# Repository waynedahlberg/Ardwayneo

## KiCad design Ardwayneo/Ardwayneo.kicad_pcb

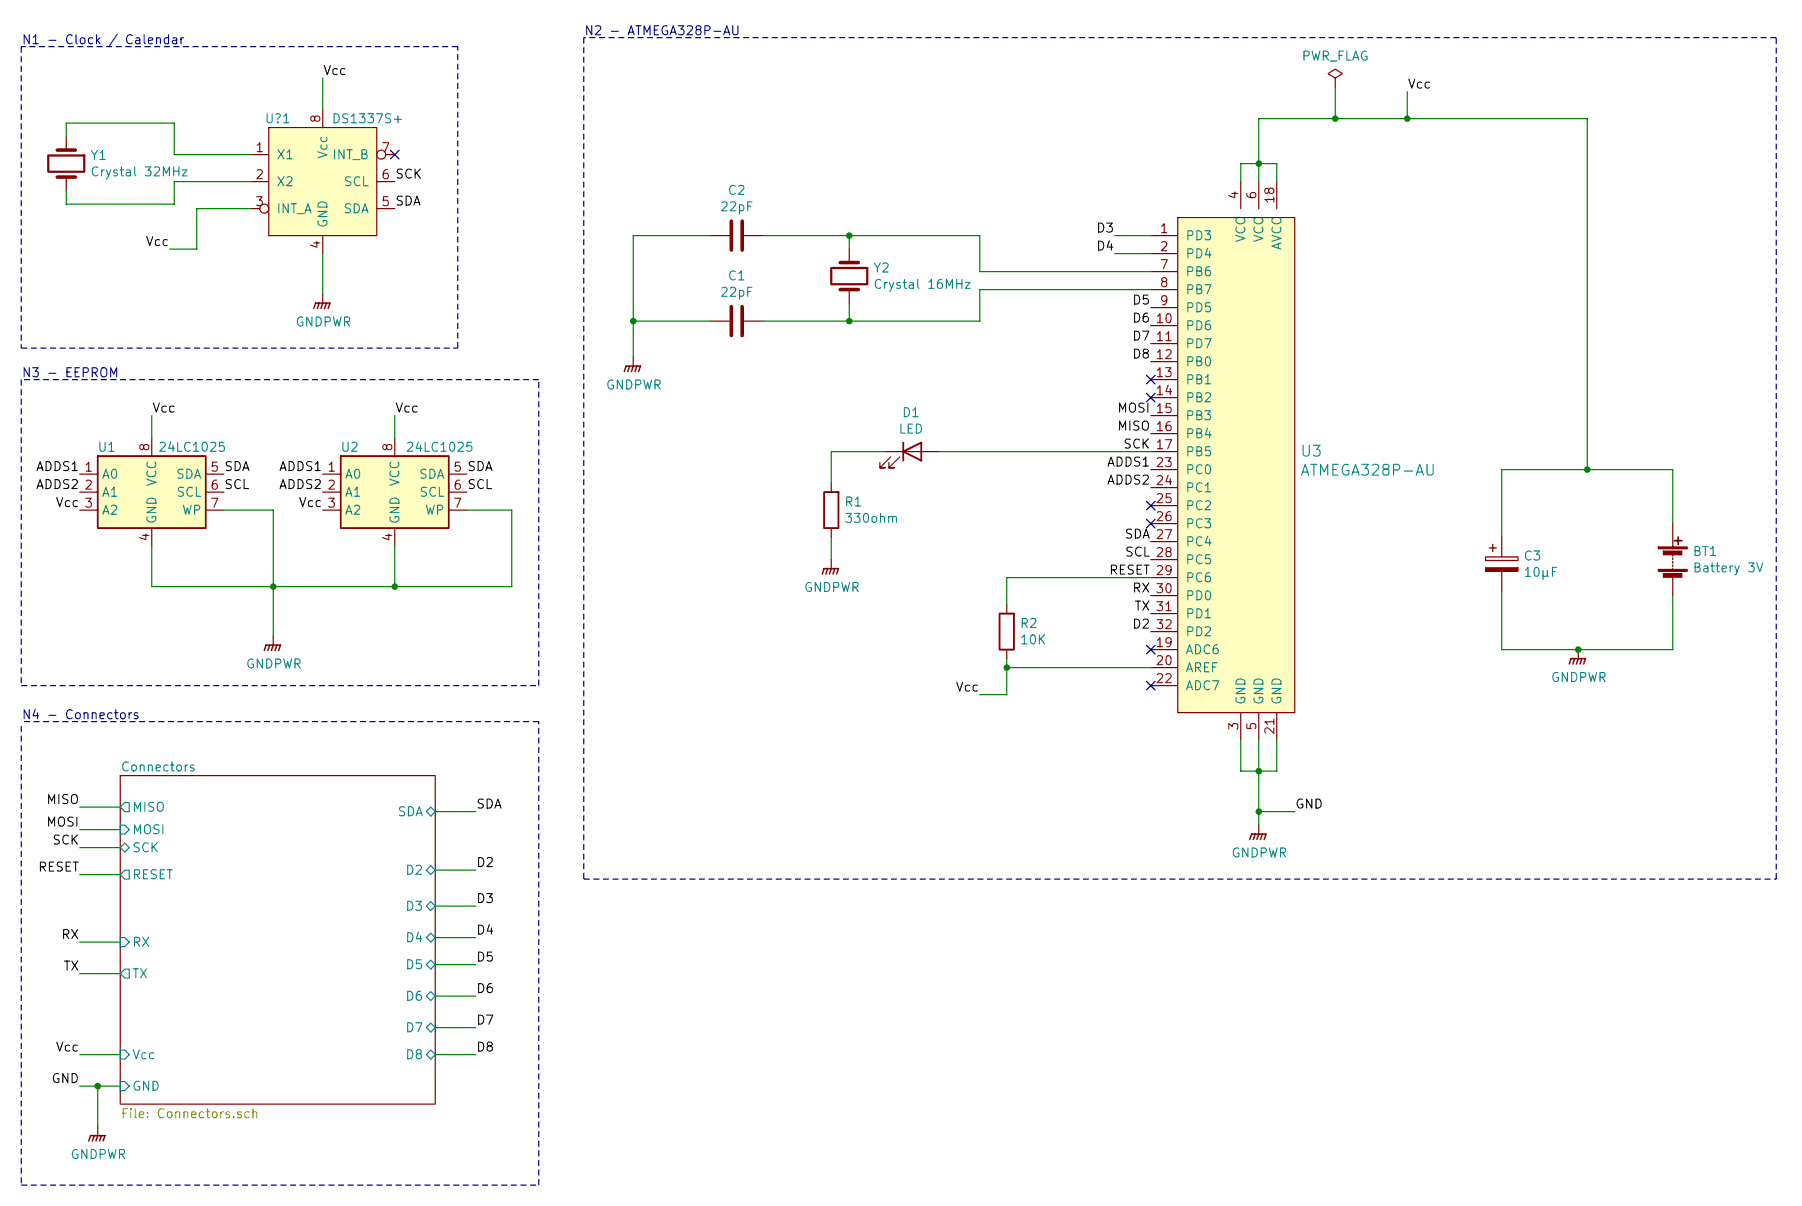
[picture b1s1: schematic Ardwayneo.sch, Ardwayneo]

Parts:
BT1: Battery 3V; PinHeader_1x02_P2.54mm_Vertical
C1, C2: 22pF; C_0805_2012Metric_Pad1.18x1.45mm_HandSolder
C3: 10µF; C_0805_2012Metric_Pad1.18x1.45mm_HandSolder
D1: LED; LED_0805_2012Metric_Pad1.15x1.40mm_HandSolder
R1: 330ohm; R_0805_2012Metric_Pad1.20x1.40mm_HandSolder
R2: 10K; R_0805_2012Metric_Pad1.20x1.40mm_HandSolder
U1, U2: 24LC1025; SOIJ-8_5.3x5.3mm_P1.27mm
U3: ATMEGA328P-AU; TQFP-32_7x7mm; MPN ATMEGA328P-AU; Digi-Key_PN ATMEGA328P-AU-ND
U?1: DS1337S+; SO-8_5.3x6.2mm_P1.27mm
Y1: Crystal 32MHz; Crystal_SMD_MicroCrystal_CC7V-T1A-2Pin_3.2x1.5mm
Y2: Crystal 16MHz; Crystal_SMD_5032-2Pin_5.0x3.2mm_HandSoldering

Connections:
/ADDS1: U1.1 (A0), U2.1 (A0), U3.23 (PC0)
/ADDS2: U1.2 (A1), U2.2 (A1), U3.24 (PC1)
/D2: U3.32 (PD2); also elsewhere on the board
/D3: U3.1 (PD3); also elsewhere on the board
/D4: U3.2 (PD4); also elsewhere on the board
/D5: U3.9 (PD5); also elsewhere on the board
/D6: U3.10 (PD6); also elsewhere on the board
/D7: U3.11 (PD7); also elsewhere on the board
/D8: U3.12 (PB0); also elsewhere on the board
/MISO: U3.16 (PB4); also elsewhere on the board
/MOSI: U3.15 (PB3); also elsewhere on the board
/RESET: R2.2, U3.29 (PC6); also elsewhere on the board
/RX: U3.30 (PD0); also elsewhere on the board
/SCK: D1.2 (A), U3.17 (PB5), U?1.6 (SCL); also elsewhere on the board
/SCL: U1.6 (SCL), U2.6 (SCL), U3.28 (PC5)
/SDA: U1.5 (SDA), U2.5 (SDA), U3.27 (PC4), U?1.5 (SDA); also elsewhere on the board
/TX: U3.31 (PD1); also elsewhere on the board
/Vcc: BT1.1 (+), C3.1, R2.1, U1.3 (A2), U1.8 (VCC), U2.3 (A2), U2.8 (VCC), U3.4 (VCC), U3.6 (VCC), U3.18 (AVCC), U3.20 (AREF), U?1.3 (INT_A), U?1.8 (Vcc); also elsewhere on the board
GNDPWR: BT1.2 (-), C1.1, C2.2, C3.2, R1.1, U1.4 (GND), U1.7 (WP), U2.4 (GND), U2.7 (WP), U3.3 (GND), U3.5 (GND), U3.21 (GND), U?1.4 (GND); also elsewhere on the board
unnamed: C1.2, U3.8 (PB7), Y2.2
unnamed: C2.1, U3.7 (PB6), Y2.1
unnamed: D1.1 (K), R1.2
unnamed 28: U?1.1 (X1), Y1.1; also elsewhere on the board
unnamed 29: U?1.2 (X2), Y1.2; also elsewhere on the board

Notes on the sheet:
N1 - Clock / Calendar
N3 - EEPROM
N2 - ATMEGA328P-AU
N4 - Connectors

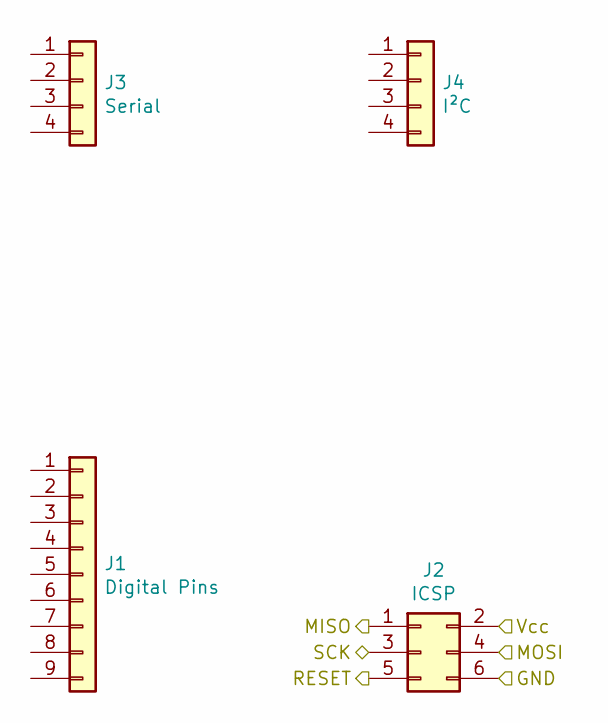
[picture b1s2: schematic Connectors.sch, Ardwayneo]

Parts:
J1: Digital Pins; PinHeader_1x09_P2.54mm_Vertical
J2: ICSP; PinSocket_2x03_P2.54mm_Vertical
J3: Serial; PinSocket_1x04_P2.54mm_Vertical
J4: I²C; PinSocket_1x04_P2.54mm_Vertical

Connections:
/D2: J1.1; also elsewhere on the board
/D3: J1.2; also elsewhere on the board
/D4: J1.3; also elsewhere on the board
/D5: J1.4; also elsewhere on the board
/D6: J1.5; also elsewhere on the board
/D7: J1.6; also elsewhere on the board
/D8: J1.7; also elsewhere on the board
/MISO: J2.1; also elsewhere on the board
/MOSI: J2.4; also elsewhere on the board
/RESET: J2.5; also elsewhere on the board
/RX: J3.3; also elsewhere on the board
/SCK: J2.3, J4.4; also elsewhere on the board
/SDA: J4.3; also elsewhere on the board
/TX: J3.4; also elsewhere on the board
/Vcc: J1.9, J2.2, J3.2, J4.2; also elsewhere on the board
GNDPWR: J1.8, J2.6, J3.1, J4.1; also elsewhere on the board

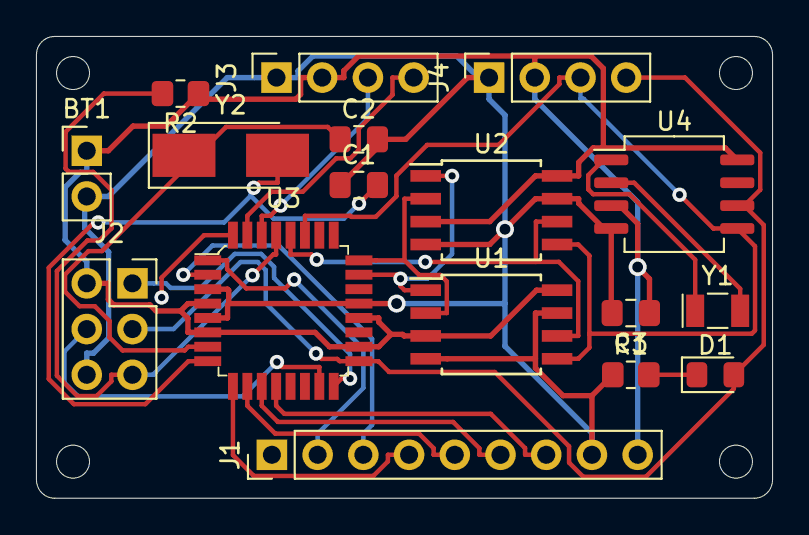
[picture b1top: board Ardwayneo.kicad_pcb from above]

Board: 4 copper layers, 40.9 x 25.7 mm, 17 parts (0 on the bottom side), 24 nets.

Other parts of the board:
U4: DS1337S+; SO-8_5.3x6.2mm_P1.27mm

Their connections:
/SCK: U4.6; also elsewhere on the board
/SDA: U4.5; also elsewhere on the board
/Vcc: U4.3, U4.8; also elsewhere on the board
GNDPWR: U4.4; also elsewhere on the board
unnamed 28: U4.1; also elsewhere on the board
unnamed 29: U4.2; also elsewhere on the board

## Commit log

2021-01-03 Initial commit
    Setup new KiCad project
2021-01-03 Update Ardwayneo.sch-bak
    Updated page frame content
2021-01-03 Add all schematic symbols
2021-01-03 Added symbols for connectors and MCU
2021-01-03 Add custom symbol
    Added custom symbol for clock IC
2021-01-03 Added missing crystal oscillators
2021-01-03 Annotation
    Annotated all symbols
2021-01-03 Completed Associations and added component values
2021-01-03 Added sheet connector pins to ATMEGA
2021-01-03 Completed wiring from connectors sheet
2021-01-03 Completed wiring root sheet
2021-01-03 Completed all wiring
2021-01-03 Added functional block descriptions
2021-01-03 Added netlist
2021-01-03 Added new layout file
2021-01-03 Setup layout, added track, via, drill presets in design rules
2021-01-03 Fixed association for capacitor footprints
2021-01-03 Initial layout distribution
2021-01-03 Refined, condensed layout
2021-01-03 Refined layout
2021-01-03 added, rounded border boundary
2021-01-03 Added mounting holes 4 corners
2021-01-03 Used 3rd pty autorouter, DRC checks out.
2021-01-03 Used autorouter to create 4 layer board
